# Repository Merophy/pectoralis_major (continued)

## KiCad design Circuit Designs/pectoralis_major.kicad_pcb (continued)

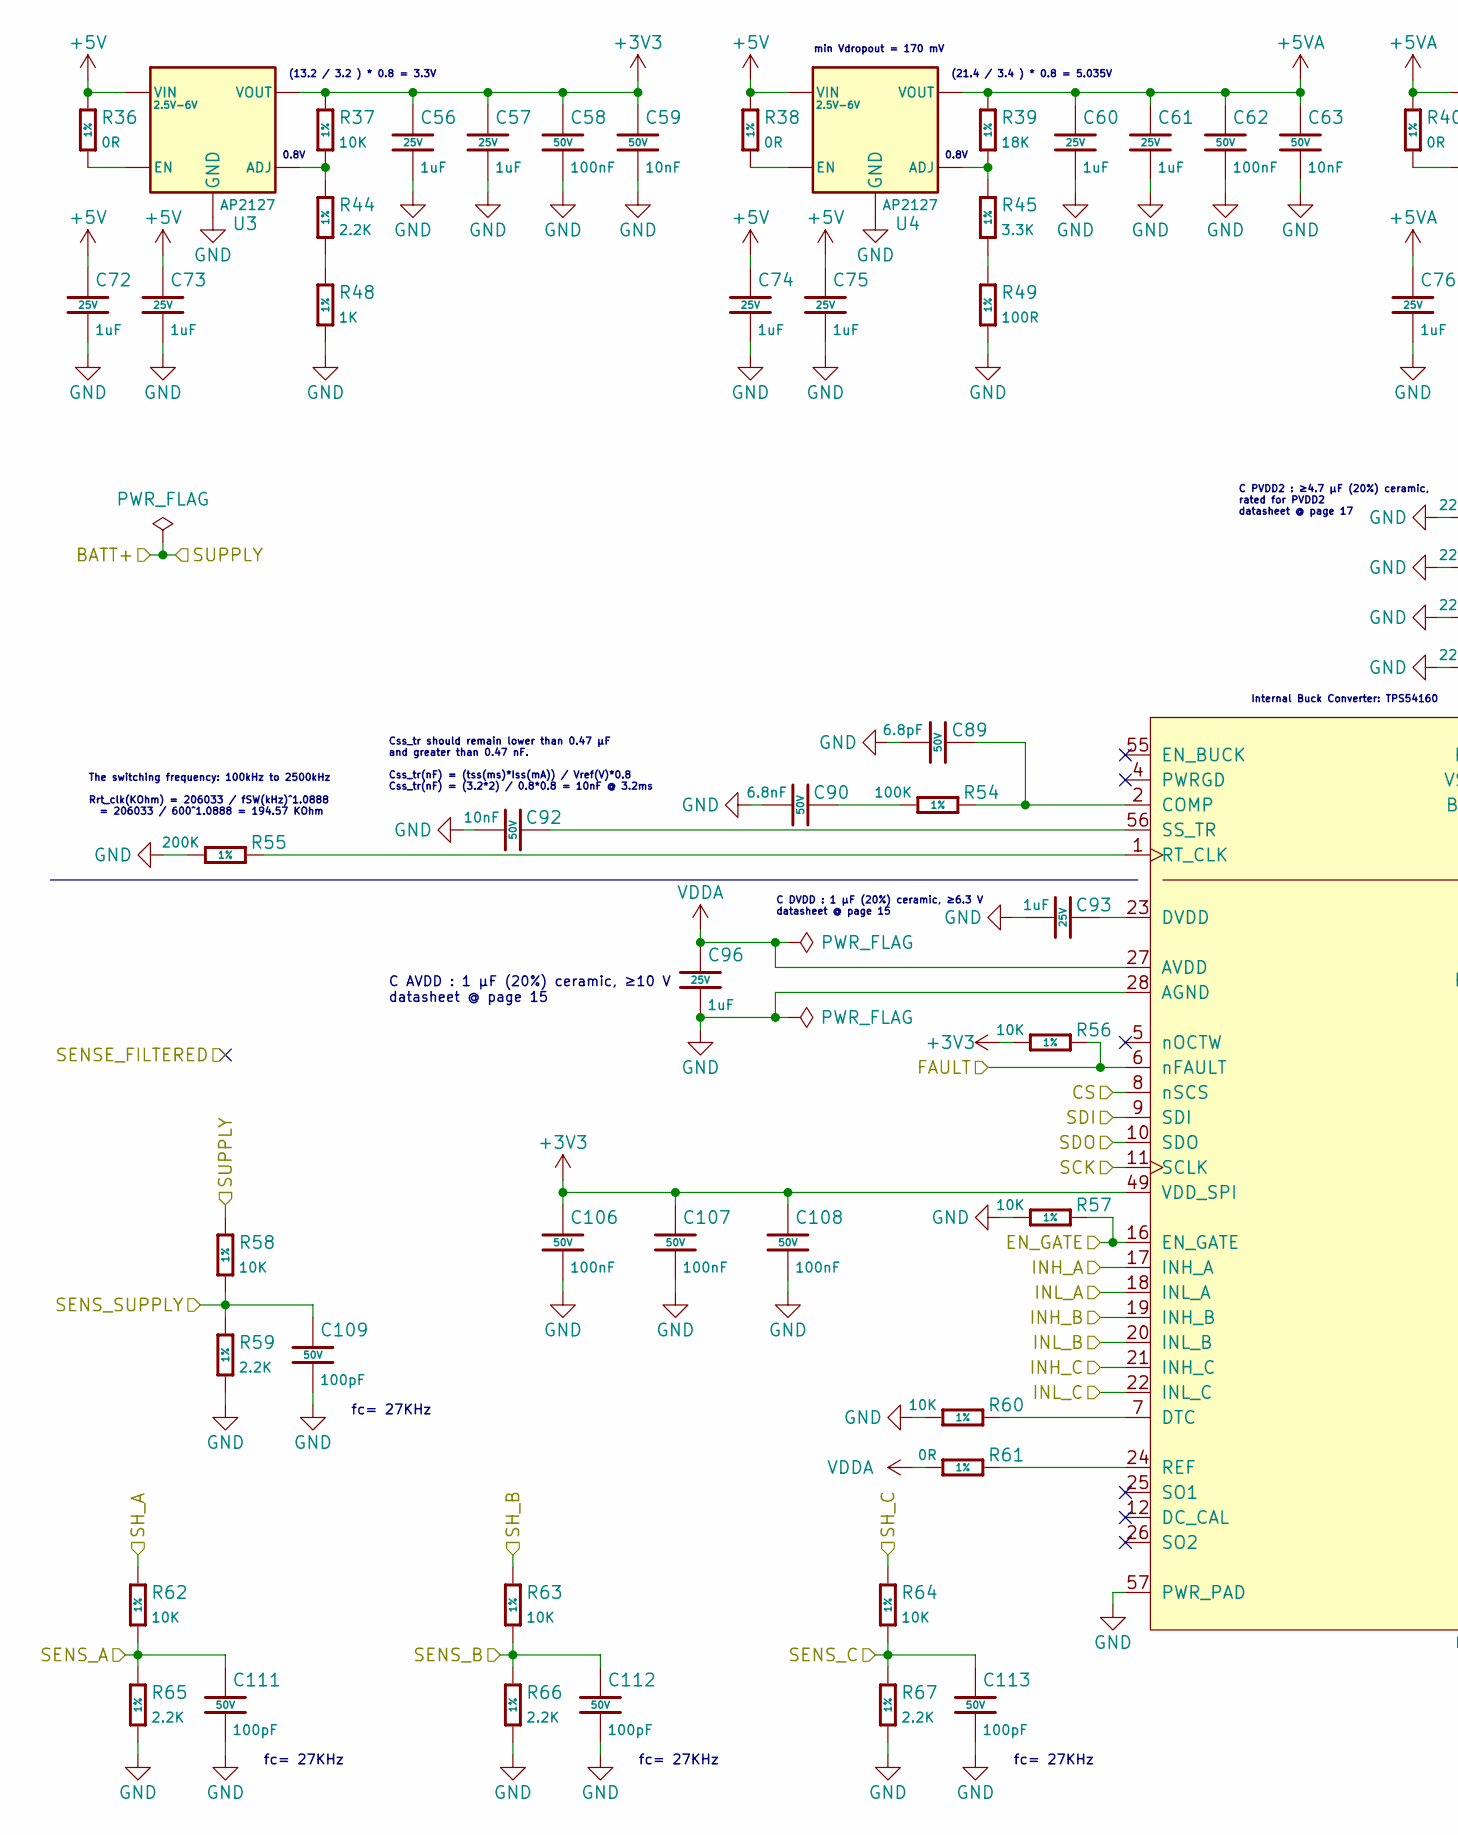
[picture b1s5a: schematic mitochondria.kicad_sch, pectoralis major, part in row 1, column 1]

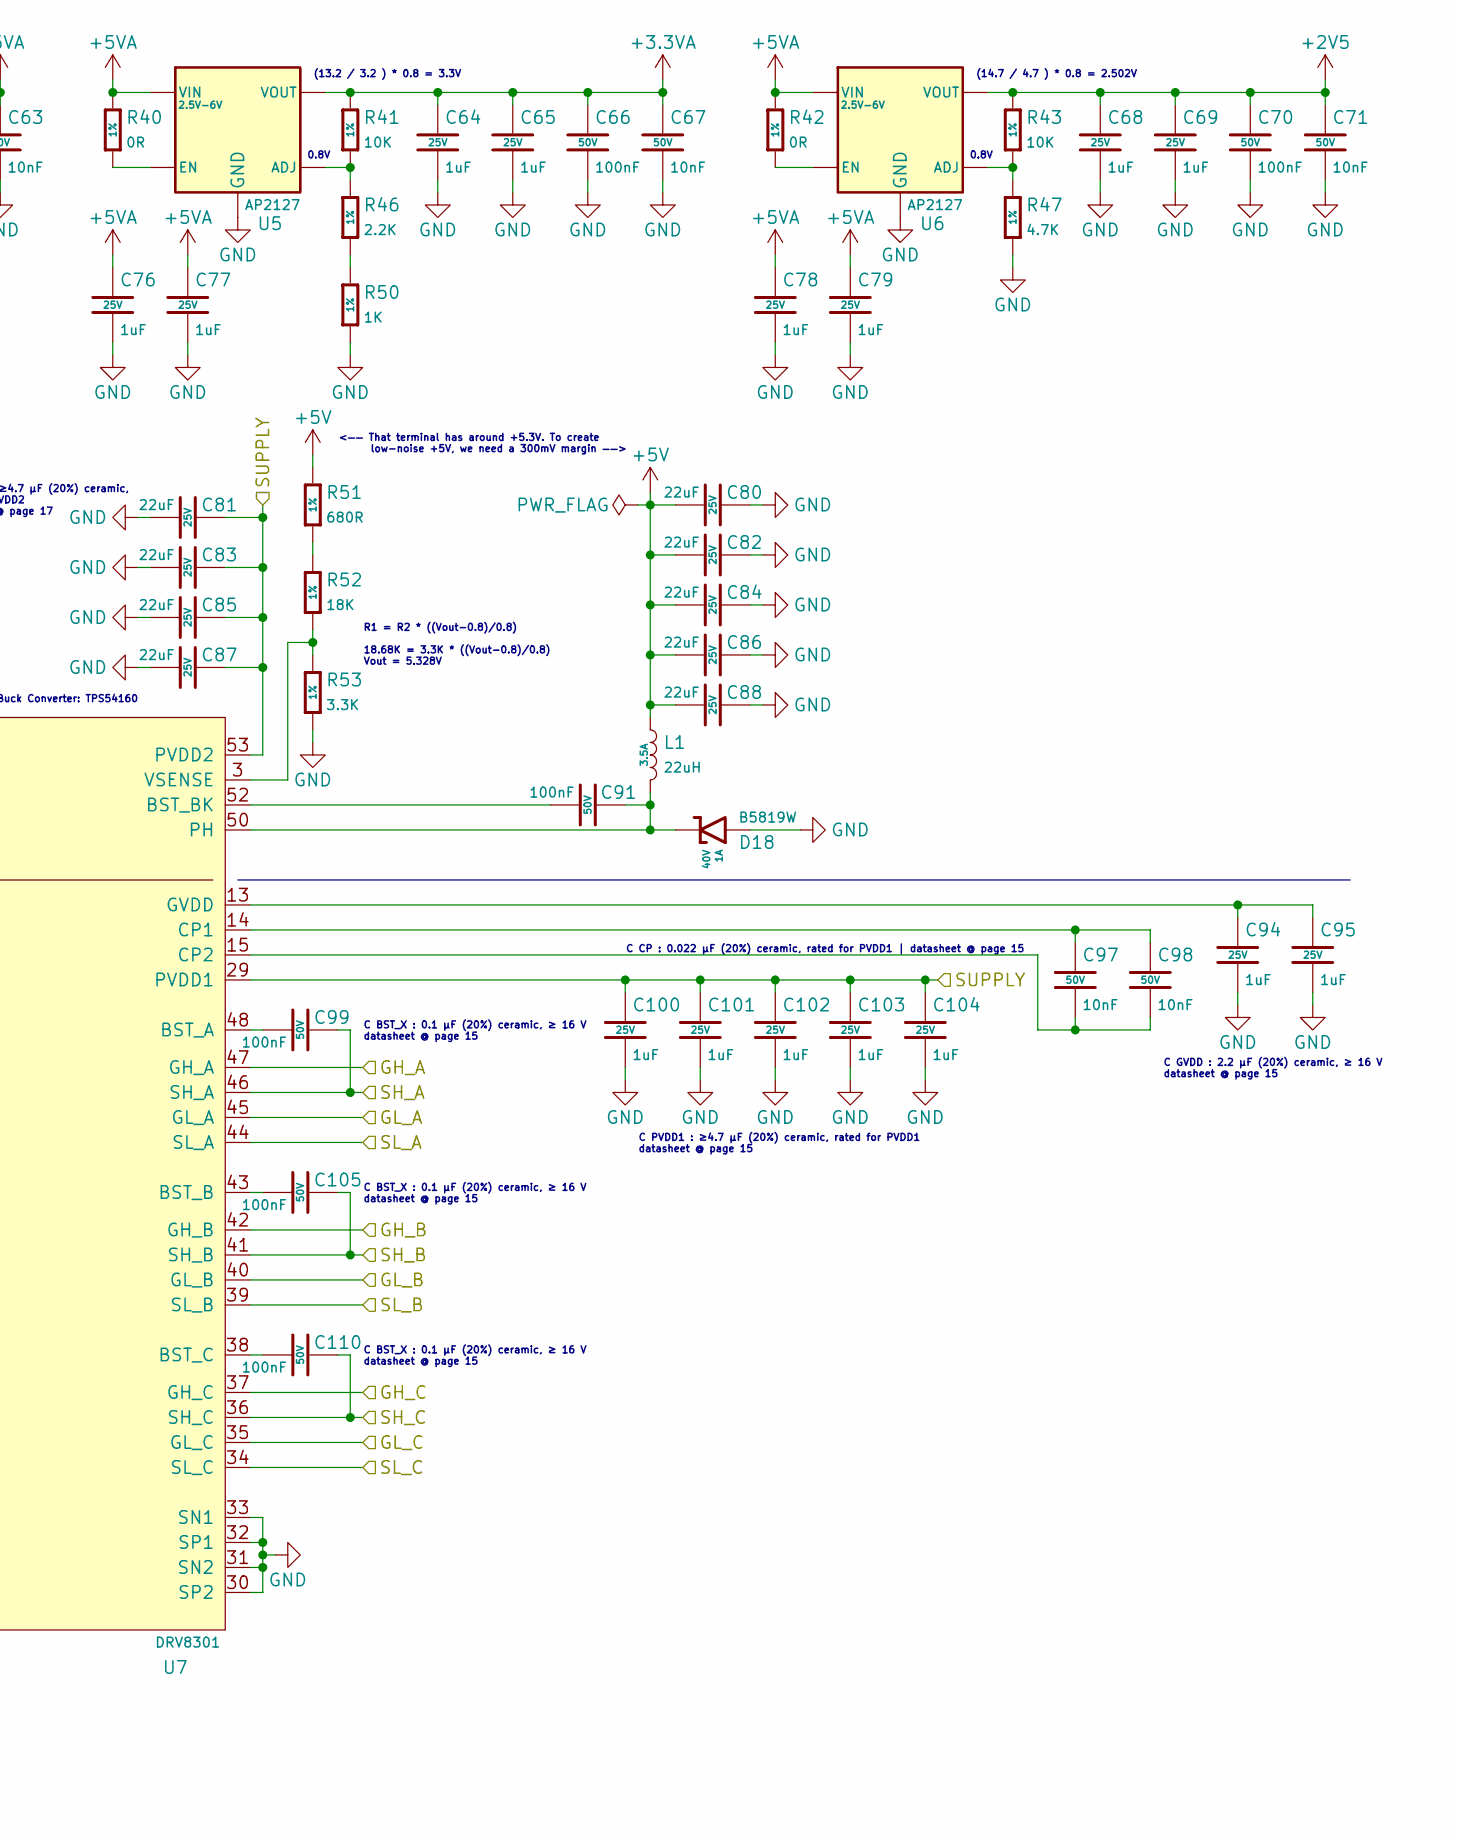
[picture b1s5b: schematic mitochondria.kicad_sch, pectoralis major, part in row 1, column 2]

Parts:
C56, C57, C60, C61, C64, C65, C68, C69, C72, C73, C74, C75, C76, C77, C78, C79, C93, C94, C95, C96, C100, C101, C102, C103, C104: 1uF; C-0402; Voltage 25V; MFR. Part # CL05A105KA5NQNC; JLCPCB Part # C52923
C58, C62, C66, C70, C91, C99, C105, C106, C107, C108, C110: 100nF; C-0402; Voltage 50V; MFR. Part # CL05B104KB54PNC; JLCPCB Part # C307331
C59, C63, C67, C71, C92, C97, C98: 10nF; C-0402; Voltage 50V; MFR. Part # CL05B103KB5NNNC; JLCPCB Part # C15195
C80, C81, C82, C83, C84, C85, C86, C87, C88: 22uF; C-0805; Voltage 25V; MFR. Part # CL21A226MAQNNNE; JLCPCB Part # C45783
C89: 6.8pF; C-0402; Voltage 50V; MFR. Part # 0402CG6R8C500NT; JLCPCB Part # C1576
C90: 6.8nF; C-0402; Voltage 50V; MFR. Part # 0402B682K500NT; JLCPCB Part # C1542
C109, C111, C112, C113: 100pF; C-0402; Voltage 50V; MFR. Part # 0402CG101J500NT; JLCPCB Part # C1546
D18: B5819W; SOD-123; Reverse Voltage 40V; MFR. Part # B5819W SL; JLCPCB Part # C8598
L1: 22uH; L-7.1-6.6; MFR Part # SMMS0630-220M; JLCPCB Part # C128694
R36, R38, R40, R42, R61: 0R; R-0402; Tolerance 1%; MFR. Part # 0402WGF0000TCE; JLCPCB Part # C17168
R37, R41, R43, R56, R57, R58, R60, R62, R63, R64: 10K; R-0402; Tolerance 1%; MFR. Part # 0402WGF1002TCE; JLCPCB Part # C25744
R39, R52: 18K; R-0402; Tolerance 1%; MFR. Part # 0402WGF1802TCE; JLCPCB Part # C25762
R44, R46, R59, R65, R66, R67: 2.2K; R-0402; Tolerance 1%; MFR. Part # 0402WGF2201TCE; JLCPCB Part # C25879
R45, R53: 3.3K; R-0402; Tolerance 1%; MFR. Part # 0402WGF3301TCE; JLCPCB Part # C25890
R47: 4.7K; R-0402; Tolerance 1%; MFR. Part # 0402WGF4701TCE; JLCPCB Part # C25900
R48, R50: 1K; R-0402; Tolerance 1%; MFR. Part # 0402WGF1001TCE; JLCPCB Part # C11702
R49: 100R; R-0402; Tolerance 1%; MFR. Part # 0402WGF1000TCE; JLCPCB Part # C25076
R51: 680R; R-0402; Tolerance 1%; MFR. Part # 0402WGF6800TCE; JLCPCB Part # C25130
R54: 100K; R-0402; Tolerance 1%; MFR. Part # 0402WGF1003TCE; JLCPCB Part # C25741
R55: 200K; R-0402; Tolerance 1%; MFR. Part # 0402WGF2003TCE; JLCPCB Part # C25764
U3, U4, U5, U6: AP2127; SOT-23-5; Operating voltage 2.5V-6V; MFR Part # AP2127K-ADJTRG1; JLCPCB Part # C96343
U7: DRV8301; HTSSOP-56-EP; MFR Part # DRV8301DCA; Digikey Part # 296-33274-5-ND

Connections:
+2V5: C68.1, C69.1, C70.1, C71.1, R43.1, U6.5 (VOUT); also elsewhere on the board
+3.3VA: C64.1, C65.1, C66.1, C67.1, R41.1, U5.5 (VOUT); also elsewhere on the board
+3V3: C56.1, C57.1, C58.1, C59.1, C106.1, C107.1, C108.1, R37.1, R56.1, U3.5 (VOUT), U7.49 (VDD_SPI); also elsewhere on the board
+5V: C72.1, C73.1, C74.1, C75.1, C80.2, C82.2, C84.2, C86.2, C88.2, L1.1, R36.1, R38.1, R51.1, U3.1 (VIN), U4.1 (VIN); also elsewhere on the board
+5VA: C60.1, C61.1, C62.1, C63.1, C76.1, C77.1, C78.1, C79.1, R39.1, R40.1, R42.1, U4.5 (VOUT), U5.1 (VIN), U6.1 (VIN); also elsewhere on the board
/powerDrivers/CS: U7.8 (nSCS); also elsewhere on the board
/powerDrivers/EN_GATE: R57.2, U7.16 (EN_GATE); also elsewhere on the board
/powerDrivers/FAULT: R56.2, U7.6 (nFAULT); also elsewhere on the board
/powerDrivers/GH_A: U7.47 (GH_A); also elsewhere on the board
/powerDrivers/GH_B: U7.42 (GH_B); also elsewhere on the board
/powerDrivers/GH_C: U7.37 (GH_C); also elsewhere on the board
/powerDrivers/GL_A: U7.45 (GL_A); also elsewhere on the board
/powerDrivers/GL_B: U7.40 (GL_B); also elsewhere on the board
/powerDrivers/GL_C: U7.35 (GL_C); also elsewhere on the board
/powerDrivers/INH_A: U7.17 (INH_A); also elsewhere on the board
/powerDrivers/INH_B: U7.19 (INH_B); also elsewhere on the board
/powerDrivers/INH_C: U7.21 (INH_C); also elsewhere on the board
/powerDrivers/INL_A: U7.18 (INL_A); also elsewhere on the board
/powerDrivers/INL_B: U7.20 (INL_B); also elsewhere on the board
/powerDrivers/INL_C: U7.22 (INL_C); also elsewhere on the board
/powerDrivers/SCK: U7.11 (SCLK); also elsewhere on the board
/powerDrivers/SDI: U7.9 (SDI); also elsewhere on the board
/powerDrivers/SDO: U7.10 (SDO); also elsewhere on the board
/powerDrivers/SENS_A: C111.1, R62.2, R65.1; also elsewhere on the board
/powerDrivers/SENS_B: C112.1, R63.2, R66.1; also elsewhere on the board
/powerDrivers/SENS_C: C113.1, R64.2, R67.1; also elsewhere on the board
/powerDrivers/SENS_SUPPLY: C109.1, R58.2, R59.1; also elsewhere on the board
/powerDrivers/SH_A: C99.2, R62.1, U7.46 (SH_A); also elsewhere on the board
/powerDrivers/SH_B: C105.2, R63.1, U7.41 (SH_B); also elsewhere on the board
/powerDrivers/SH_C: C110.2, R64.1, U7.36 (SH_C); also elsewhere on the board
GND: C56.2, C57.2, C58.2, C59.2, C60.2, C61.2, C62.2, C63.2, C64.2, C65.2, C66.2, C67.2, C68.2, C69.2, C70.2, C71.2, C72.2, C73.2, C74.2, C75.2, C76.2, C77.2, C78.2, C79.2, C80.1, C81.2, C82.1, C83.2, C84.1, C85.2, C86.1, C87.2, C88.1, C89.2, C90.1, C92.1, C93.1, C94.2, C95.2, C96.2, C100.2, C101.2, C102.2, C103.2, C104.2, C106.2, C107.2, C108.2, C109.2, C111.2, C112.2, C113.2, D18.2 (A), R47.2, R48.2, R49.2, R50.2, R53.2, R55.1, R57.1, R59.2, R60.1, R65.2, R66.2, R67.2, U3.2 (GND), U4.2 (GND), U5.2 (GND), U6.2 (GND), U7.28 (AGND), U7.30 (SP2), U7.31 (SN2), U7.32 (SP1), U7.33 (SN1), U7.34 (SL_C), U7.39 (SL_B), U7.44 (SL_A), U7.57 (PWR_PAD); also elsewhere on the board
unnamed: C89.1, R54.2, U7.2 (COMP)
unnamed: C90.2, R54.1
unnamed: C91.1, U7.52 (BST_BK)
unnamed: C91.2, D18.1 (K), L1.2, U7.50 (PH), U7.51 (PH)
unnamed: C92.2, U7.56 (SS_TR)
unnamed: C93.2, U7.23 (DVDD)
unnamed: C94.1, C95.1, U7.13 (GVDD)
unnamed: C97.1, C98.1, U7.14 (CP1)
unnamed: C97.2, C98.2, U7.15 (CP2)
unnamed: C99.1, U7.48 (BST_A)
unnamed: C105.1, U7.43 (BST_B)
unnamed: C110.1, U7.38 (BST_C)
unnamed: R36.2, U3.3 (EN)
unnamed: R37.2, R44.1, U3.4 (ADJ)
unnamed: R38.2, U4.3 (EN)
unnamed: R39.2, R45.1, U4.4 (ADJ)
unnamed: R40.2, U5.3 (EN)
unnamed: R41.2, R46.1, U5.4 (ADJ)
unnamed: R42.2, U6.3 (EN)
unnamed: R43.2, R47.1, U6.4 (ADJ)
unnamed: R44.2, R48.1
unnamed: R45.2, R49.1
unnamed: R46.2, R50.1
unnamed: R51.2, R52.1
unnamed: R52.2, R53.1, U7.3 (VSENSE)
unnamed: R55.2, U7.1 (RT_CLK)
unnamed: R60.2, U7.7 (DTC)
unnamed: R61.2, U7.24 (REF)
PVDD2: C81.1, C83.1, C85.1, C87.1, C100.1, C101.1, C102.1, C103.1, C104.1, R58.1, U7.29 (PVDD1), U7.53 (PVDD2), U7.54 (PVDD2); also elsewhere on the board
VDDA: C96.1, R61.1, U7.27 (AVDD)

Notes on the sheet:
0.8V
Css_tr should remain lower than 0.47 μF and greater than 0.47 nF. Css_tr(nF) = (tss(ms)*Iss(mA)) / Vref(V)*0.8 Css_tr(nF) = (3.2*2) / 0.8*0.8 = 10nF @ 3.2ms
C PVDD1 : ≥4.7 μF (20%) ceramic, rated for PVDD1 datasheet @ page 15
fc= 27KHz
Internal Buck Converter: TPS54160
<—— That terminal has around +5.3V. To create low-noise +5V, we need a 300mV margin ——>
C DVDD : 1 μF (20%) ceramic, ≥6.3 V datasheet @ page 15
(14.7 / 4.7 ) * 0.8 = 2.502V
C PVDD2 : ≥4.7 μF (20%) ceramic, rated for PVDD2 datasheet @ page 17
(13.2 / 3.2 ) * 0.8 = 3.3V
R1 = R2 * ((Vout-0.8)/0.8) 18.68K = 3.3K * ((Vout-0.8)/0.8) Vout = 5.328V
C BST_X : 0.1 μF (20%) ceramic, ≥ 16 V datasheet @ page 15
C GVDD : 2.2 μF (20%) ceramic, ≥ 16 V datasheet @ page 15
(21.4 / 3.4 ) * 0.8 = 5.035V
C AVDD : 1 μF (20%) ceramic, ≥10 V datasheet @ page 15
The switching frequency: 100kHz to 2500kHz Rrt_clk(KOhm) = 206033 / fSW(kHz)^1.0888 = 206033 / 600^1.0888 = 194.57 KOhm
min Vdropout = 170 mV
C CP : 0.022 μF (20%) ceramic, rated for PVDD1 | datasheet @ page 15

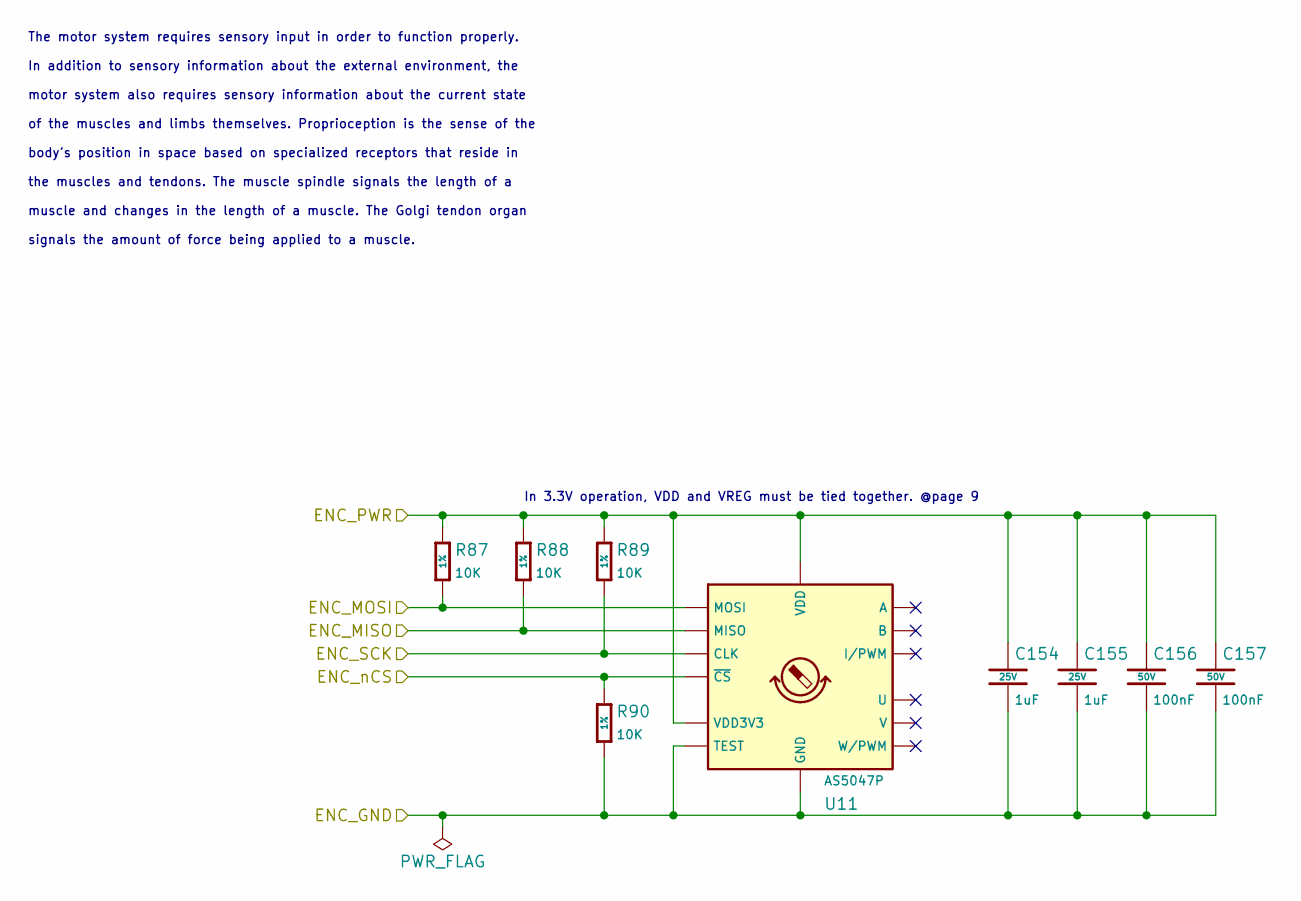
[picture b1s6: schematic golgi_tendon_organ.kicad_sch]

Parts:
C154, C155: 1uF; C-0402; Voltage 25V; MFR. Part # CL05A105KA5NQNC; JLCPCB Part # C52923
C156, C157: 100nF; C-0402; Voltage 50V; MFR. Part # CL05B104KB54PNC; JLCPCB Part # C307331
R87, R88, R89, R90: 10K; R-0402; Tolerance 1%; MFR. Part # 0402WGF1002TCE; JLCPCB Part # C25744
U11: AS5047P; TSSOP-14_4.4x5mm_P0.65mm; MFR Part # AS5047P-ATSM; Digikey Part # AS5047P-ATSMCT-ND

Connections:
/Proprioception/ENC_GND: C154.2, C155.2, C156.2, C157.2, R90.2, U11.5 (TEST), U11.13 (GND); also elsewhere on the board
/Proprioception/ENC_MISO: R88.2, U11.3 (MISO); also elsewhere on the board
/Proprioception/ENC_MOSI: R87.2, U11.4 (MOSI); also elsewhere on the board
/Proprioception/ENC_PWR: C154.1, C155.1, C156.1, C157.1, R87.1, R88.1, R89.1, U11.11 (VDD), U11.12 (VDD3V3); also elsewhere on the board
/Proprioception/ENC_SCK: R89.2, U11.2 (CLK); also elsewhere on the board
/Proprioception/ENC_nCS: R90.1, U11.1 (~CS); also elsewhere on the board

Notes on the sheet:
In 3.3V operation, VDD and VREG must be tied together. @page 9
The motor system requires sensory input in order to function properly. In addition to sensory information about the external environment, the motor system also requires sensory information about the current state of the muscles and limbs themselves. Proprioception is the sense of the body’s positio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

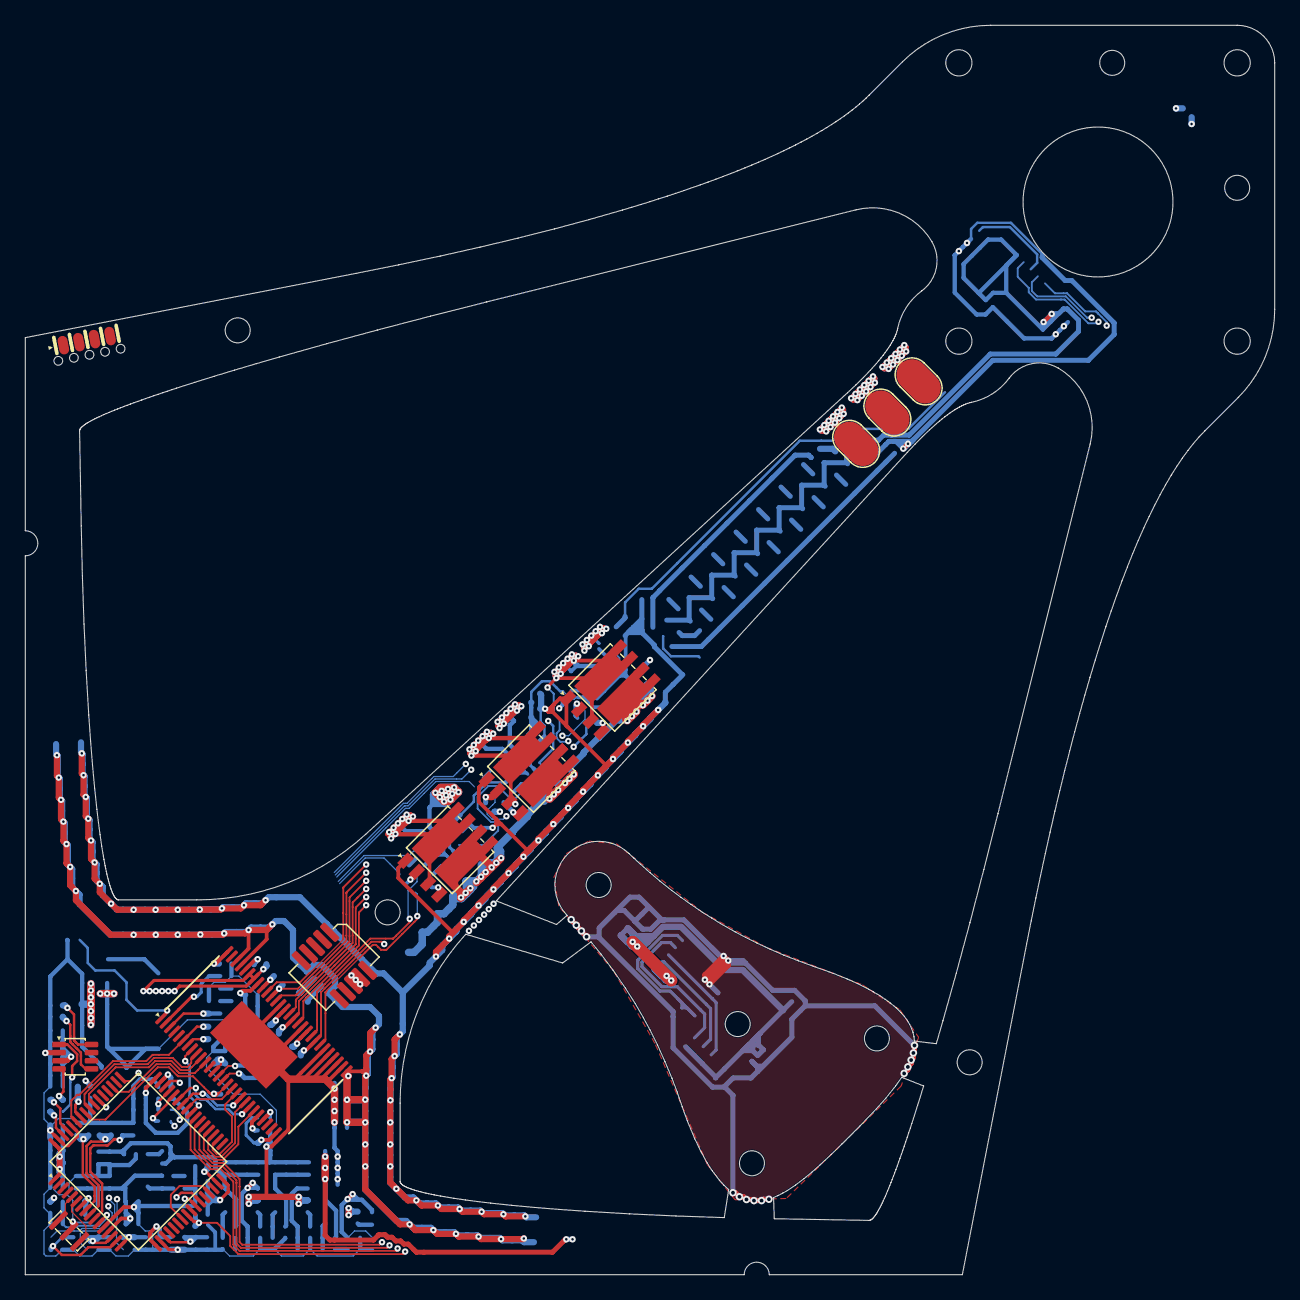
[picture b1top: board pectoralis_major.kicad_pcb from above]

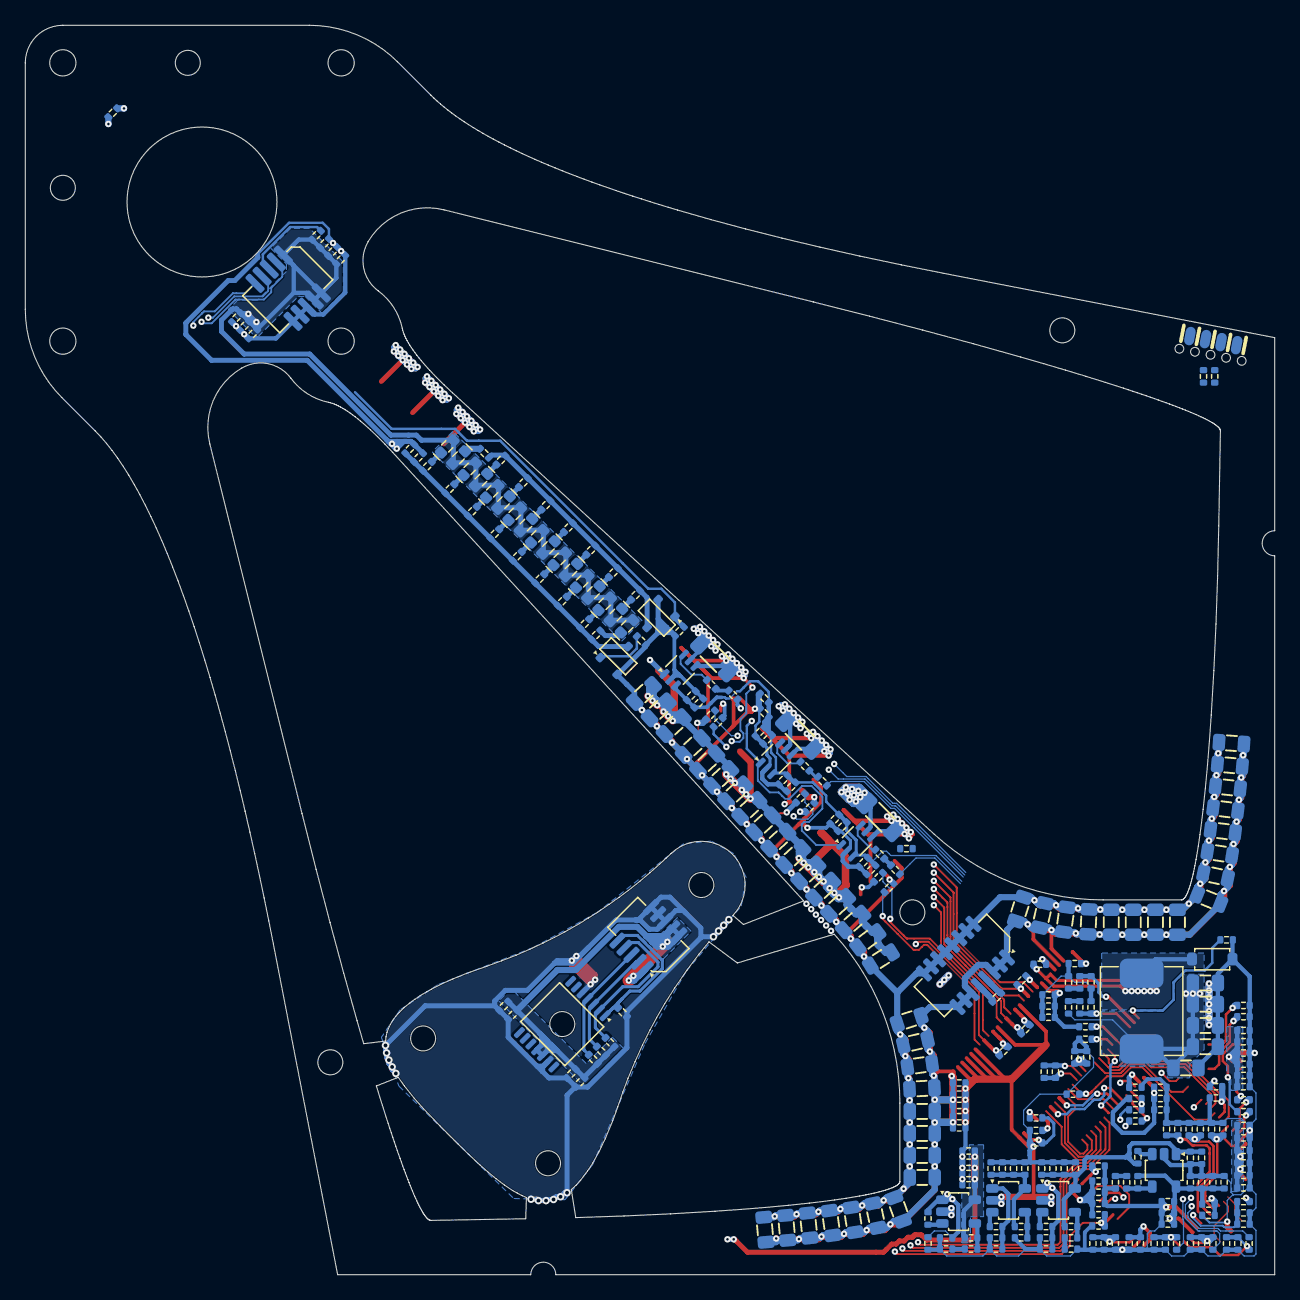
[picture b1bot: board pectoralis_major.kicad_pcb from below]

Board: 4 copper layers, 100.0 x 100.0 mm, 293 parts (281 on the bottom side), 136 nets.

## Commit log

2022-02-15 initialized the circuit design files
2022-02-15 added submodules
2022-02-17 added the MCU, duplicated the LEDs for bottom side, changed the can driver to tcan330
2022-02-17 added buck converter's components
2022-02-19 added motor driver and adjustable regulators. Now, it is the time to start the detailed review
2022-02-19 created golgi_tendon_organ page
2022-02-19 added hal sensor
2022-02-20 added servo control input feature
2022-02-20 edited myofibril file, added a related image about myofibrils
2022-02-21 edited the buck converter in the motor driver IC
2022-02-25 tuned the compansation at the buck driver
2022-02-25 migration! KiCad 6.0
2022-02-28 deleted previous version files
2022-03-01 changed the LED packages, edited field reference positions
2022-03-02 added a diode package to the libs
2022-03-03 created and added the packages called SOT-23-5 and SOT-23-8 to the libraries
2022-03-04 edited the motor driver's and the current amplifier's packages
2022-03-05 added last Small-Outline packaged component to the library and updated the design
2022-03-06 done all the packages and migrations. Now, time to start to route the module
2022-03-09 placed LEDs, mosfets, bulk capacitors
2022-03-12 placed current shunt circuits and mosfets
2022-03-12 First placement of the MCU Page's components are done
2022-03-12 placing all the regulators are done
2022-03-12 placed all the components except magnetic sensor board
2022-03-12 drew the traces in the light section
2022-03-30 done placing and routing of the golgi tendon organ
2022-03-31 done the connection between the MCU and the motor driver
2022-04-10 done all the tracing between the driver and the mosfets
2022-04-14 done mosfet tracing
